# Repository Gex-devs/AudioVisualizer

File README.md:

# STM32 Audio visualizer DOT MATRIX

Audio Visualizer based on STM32 bluepill utilizing Fast FFT and hacky trick to make the Matrix LED working nicely together. 

## Compact Size

Made a Add-on type PCB that laches on the back of the LED matrix.

## Components 
The Audio Visualizer features Real-time audio visualization with Fast Fourier Transform (FFT) to accurately visualize real audio frequencies rather than just detecting high or low noise levels.

* STM32 Bluepill
* MAX4466 Microphone Module
* 8x8 Matrix LED * 4

## Software Used

* [Kicad](https://www.kicad.org/) : PCB Design 
* [STM32MAX](https://www.st.com/en/development-tools/stm32cubemx.html) : Project Configurator 
* [T-filter](http://t-filter.engineerjs.com/) : Desgning Fir filter

## Tools Used

* Lab power supply
* Oscilloscope 
* ST-LINK/V2 debugger

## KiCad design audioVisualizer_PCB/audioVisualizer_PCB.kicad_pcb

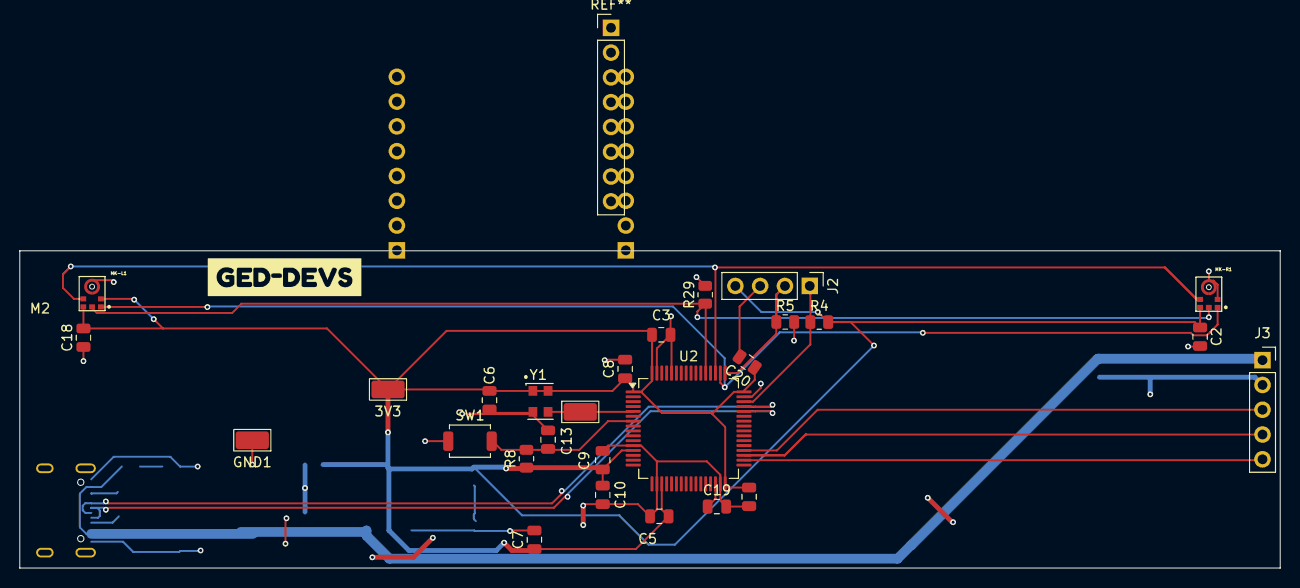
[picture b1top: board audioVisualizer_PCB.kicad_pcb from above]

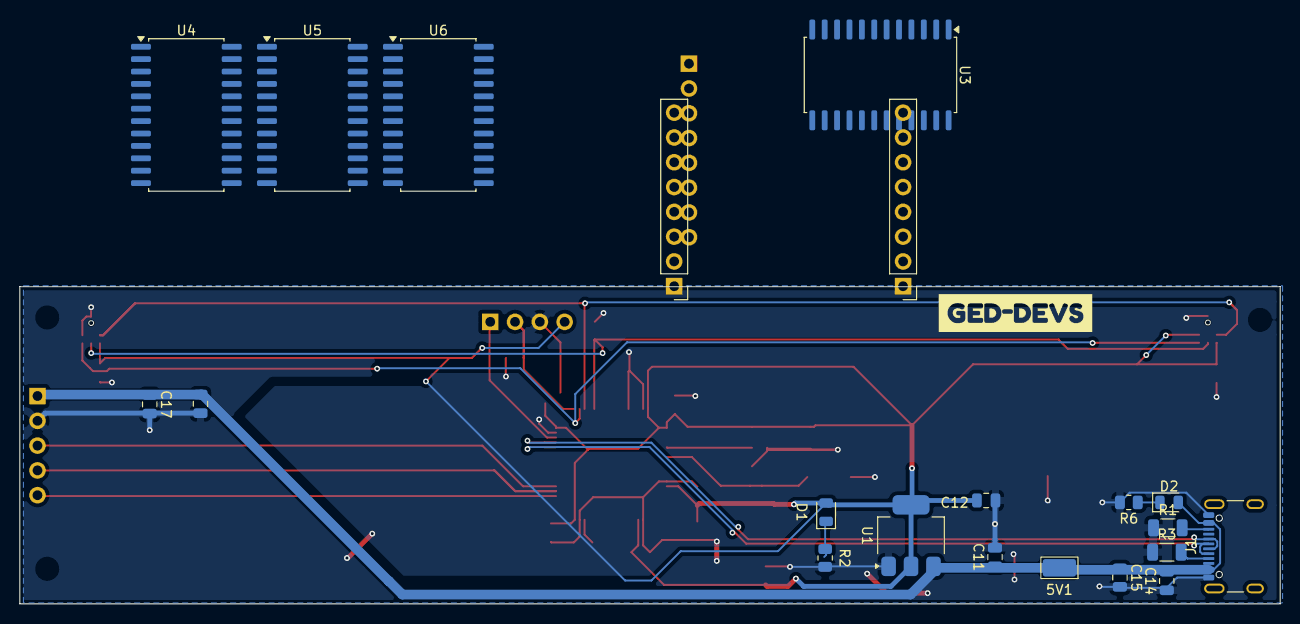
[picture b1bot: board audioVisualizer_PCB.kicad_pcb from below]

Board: 2 copper layers, 129.1 x 32.5 mm, 49 parts (21 on the bottom side), 37 nets.

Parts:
3V3: TestPoint_3V3; TestPoint_Keystone_5015_Micro_Mini
5V1: TestPoint_5V; TestPoint_Keystone_5015_Micro_Mini
C2, C3, C4, C5, C6, C8, C9, C13, C14, C16, C18, C20: 100nF; C_0805_2012Metric
C7: 4.7uF; C_0805_2012Metric
C10, C11, C12: 10uF; C_0805_2012Metric
C15, C17: 1uF; C_0805_2012Metric
C19: 2.2uF; C_0805_2012Metric
CRYS_25: CRYS_25; TestPoint_Keystone_5015_Micro_Mini
D1, D2: LED; LED_0805_2012Metric
GND1: TestPoint_5V; TestPoint_Keystone_5015_Micro_Mini
J1: USB_C_16P; USB_C_Receptacle_GCT_USB4105-xx-A_16P_TopMnt_Horizontal
J2: SWD_DEBUG; PinHeader_1x04_P2.54mm_Vertical
J3: SPI_LED_MATRIX; PinSocket_1x05_P2.54mm_Vertical
J4: Conn_01x14_Socket; PinSocket_1x14_P2.54mm_Vertical
MK-L1: INMP43434-R; MIC_ICS-43434
MK-R1: INMP43434-L; MIC_ICS-43434
R1, R3: 5.1k; R_1206_3216Metric
R2: 10Ω; R_0805_2012Metric
R4, R5, R8: 10k; R_0805_2012Metric
R6: 100Ω; R_0805_2012Metric
R29: 100k; R_0805_2012Metric
SW1: SW_Push; SW_SPST_TS-1088-xR020
U1: AMS1117-3.3; SOT-223-3_TabPin2
U2: STM32F401RETx; LQFP-64_10x10mm_P0.5mm
U3, U4, U5, U6: MAX7219; SOIC-24W_7.5x15.4mm_P1.27mm
Y1: ASE-25MHz; Oscillator_SMD_EuroQuartz_XO32-4Pin_3.2x2.5mm
kibuzzard-69F6314F, kibuzzard-69F6314F#2: G***; kibuzzard-69F6314F

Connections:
+3.3V: 3V3.1 (1_1), C2.1, C3.1, C4.1, C5.1, C6.2, C7.1, C8.1, C9.1, C10.1, C12.1, C18.2, C20.1, D1.2 (A), J2.4, MK-L1.2 (L/R), MK-L1.5 (VDD), MK-R1.5 (VDD), R4.2, R8.1, U1.2 (VO), U2.1 (VBAT), U2.13 (VREF+), U2.19 (VDD), U2.32 (VDD), U2.48 (VDD), U2.64 (VDD), Y1.1 (EN), Y1.4 (Vdd)
+5V: 5V1.1 (1_1), C11.1, C14.2, C15.1, C16.2, C17.1, D2.2 (A), J1.A4 (VBUS), J1.A9 (VBUS), J1.B4 (VBUS), J1.B9 (VBUS), J3.1 (VCC), U1.3 (VI), U3.19 (V+), U4.19 (V+), U5.19 (V+), U6.19 (V+)
/CRYS_OUT: CRYS_25.1 (1_1), U2.5 (PH0), Y1.3 (OUT)
GND: C2.2, C3.2, C4.2, C5.2, C6.1, C7.2, C8.2, C9.2, C10.2, C11.2, C12.2, C13.2, C14.1, C15.2, C16.1, C17.2, C18.1, C19.2, C20.2, GND1.1 (1_1), J1.A1 (GND), J1.A12 (GND), J1.B1 (GND), J1.B12 (GND), J2.3, J3.2 (GND), MK-L1.3 (GND), MK-R1.2 (L/R), MK-R1.3 (GND), R1.1, R2.2, R3.1, R5.2, R6.2, R29.2, SW1.1, U1.1 (GND), U2.12 (VSSA), U2.18 (VSS), U2.31 (VSS), U2.47 (VSS), U2.60 (BOOT0), U2.63 (VSS), U3.4 (GND), U3.9 (GND), U4.4 (GND), U4.9 (GND), U5.4 (GND), U5.9 (GND), U6.4 (GND), U6.9 (GND), Y1.2 (GND)
MIC_SCK: MK-L1.4 (SCK), MK-R1.4 (SCK), U2.51 (PC10)
MIC_SD: MK-L1.6 (SD), MK-R1.6 (SD), R29.1, U2.53 (PC12)
MIC_WS: MK-L1.1 (WS), MK-R1.1 (WS), U2.50 (PA15)
unnamed: D1.1 (K), R2.1
unnamed: D2.1 (K), R6.1
unnamed: J1.A5 (CC1), R3.2
unnamed: J1.B5 (CC2), R1.2
unnamed: J4.1 (Pin_1_1), U3.14 (SEG_A)
unnamed: J4.2 (Pin_2_2), U3.16 (SEG_B)
unnamed: J4.3 (Pin_3_3), U3.20 (SEG_C)
unnamed: J4.4 (Pin_4_4), U3.23 (SEG_D)
unnamed: J4.5 (Pin_5_5), U3.21 (SEG_E)
unnamed: J4.6 (Pin_6_6), U3.15 (SEG_F)
unnamed: J4.7 (Pin_7_7), U3.17 (SEG_G)
unnamed: J4.8 (Pin_8_8), U3.22 (SEG_DP)
unnamed: J4.7 (Pin_9_9), U3.2 (DIG_0)
unnamed: J4.8 (Pin_10_10), U3.11 (DIG_1)
unnamed: J4.3 (Pin_11_11), U3.6 (DIG_2)
unnamed: J4.4 (Pin_12_12), U3.7 (DIG_3)
unnamed: J4.5 (Pin_13_13), U3.3 (DIG_4)
unnamed: J4.6 (Pin_14_14), U3.10 (DIG_5)
unnamed: C13.1, R8.2, SW1.2, U2.7 (NRST)
unnamed: C19.1, U2.30 (VCAP1)
unnamed: U3.24 (DOUT), U4.1 (DIN)
unnamed: U4.24 (DOUT), U5.1 (DIN)
unnamed: U5.24 (DOUT), U6.1 (DIN)
SPI_CLK: J3.5 (CLK), U2.34 (PB13), U3.13 (CLK), U4.13 (CLK), U5.13 (CLK), U6.13 (CLK)
SPI_CS: J3.4 (CS), U2.35 (PB14), U3.12 (LOAD), U4.12 (LOAD), U5.12 (LOAD), U6.12 (LOAD)
SPI_DIN: J3.3 (DIN), U2.36 (PB15), U3.1 (DIN)
SWCLK: J2.2, R5.1, U2.49 (PA14)
SWDIO: J2.1, R4.1, U2.46 (PA13)
USB_D+: J1.A6 (D+), J1.B6 (D+), U2.45 (PA12)
USB_D-: J1.A7 (D-), J1.B7 (D-), U2.44 (PA11)

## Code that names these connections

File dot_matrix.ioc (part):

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Mcu.Name=STM32F401R(D-E)Tx
Mcu.Package=LQFP64
Mcu.UserName=STM32F401RETx
PA0-WKUP.Signal=S_TIM2_CH1_ETR
PA11.Mode=Host_Only
PA11.Signal=USB_OTG_FS_DM
PA12.Mode=Host_Only
PA12.Signal=USB_OTG_FS_DP
PA13.Mode=Serial_Wire
PA13.Signal=SYS_JTMS-SWDIO
PA14.Mode=Serial_Wire
PA14.Signal=SYS_JTCK-SWCLK
PA15.Mode=Half_Duplex_Master
PA15.Signal=I2S3_WS
PA9.Mode=Activate_VBUS
PA9.Signal=USB_OTG_FS_VBUS
PB13.Mode=Simplex_Bidirectional_Master
PB13.Signal=SPI2_SCK
PB14.Signal=GPIO_Output
PB15.Mode=Simplex_Bidirectional_Master
PB15.Signal=SPI2_MOSI
PC10.Mode=Half_Duplex_Master
PC10.Signal=I2S3_CK
PC12.Mode=Half_Duplex_Master
PC12.Signal=I2S3_SD
PH0\ -\ OSC_IN.Mode=HSE-External-Clock-Source
PH0\ -\ OSC_IN.Signal=RCC_OSC_IN
PH1\ -\ OSC_OUT.Mode=HSE-External-Clock-Source
PH1\ -\ OSC_OUT.Signal=RCC_OSC_OUT
RCC.HSE_VALUE=25000000
RCC.SYSCLKFreq_VALUE=84000000
RCC.SYSCLKSource=RCC_SYSCLKSOURCE_PLLCLK
board=custom

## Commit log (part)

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2025-04-11 init
2025-04-20 Working module with LED matrix library modification
2025-04-20 Added video and image
2025-07-30 added the working libraries
2025-08-01 applied hann window and added high-pass filter, good visuals
2025-08-01 updated gitignore
2025-08-01 fixed visual mapping, Issue still in Bar index 0 - 10
2025-08-08 added filter, updated ReadME, added PCB
2025-08-08 updated read me
2025-08-08 Moved the interactive BOM to root for deployment
2025-08-19 added fritzing project for prototype
2025-08-19 added image of the Printed pcb
2025-08-28 unfinished workflow and update on the TH of the PCB footprint
2025-08-28 Fixed headerpin diameter, updated workflow
2025-08-28 workflow fix
2025-08-28 Update schematic preview [skip ci]
2025-08-28 testing workflow
2025-10-08 Added additional omni-directional smd mic, not routed or programmed
2026-01-30 update on readme
2026-02-14 break em out
2026-03-20 removed big video file
2026-04-14 updated setting to include all libraries; was causing issues during compilation
2026-04-14 migration to stm32f401
2026-04-20 changed mcu; implemented i2s succesfully; working fft; working visualizer; fixed clock issue; visualizer needs enhancement
2026-04-21 added rebinning but needs polishing
2026-04-22 clean up and similification
2026-04-25 embeddeding the mcu is harder than I thought
2026-04-30 added stereo mics; setup usb-c;fixed timer issue for led matrix; using external clock
2026-05-02 finished pcb ready for production
2026-05-02 updated preview video
2026-05-02 updated interactive bom
2026-05-03 removed history
2026-05-06 updated kicad release to the latest version
2026-05-06 dummy test for github action
2026-05-15 reflect on code as well
2026-05-18 removed unused schematic
2026-06-09 manually routed the tracks; switch LEFT/RIGHT mic
2026-06-24 added cap for vref pin
